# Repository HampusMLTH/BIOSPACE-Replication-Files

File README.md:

# BIOSPACE Replication Files

Here are files for replicating BIOSPACE as documented in Månefjord, H., M. Li, C. Brackmann, N. Reistad, A. Runemark, J. Rota, B. Anderson, J. T. Zoueu, A. Merdasa and M. Brydegaard (2022). "A biophotonic platform for quantitative analysis in the spatial, spectral, polarimetric, and goniometric domains." Review of Scientific Instruments 93(11).

Reach out to me if something is missing or unclear

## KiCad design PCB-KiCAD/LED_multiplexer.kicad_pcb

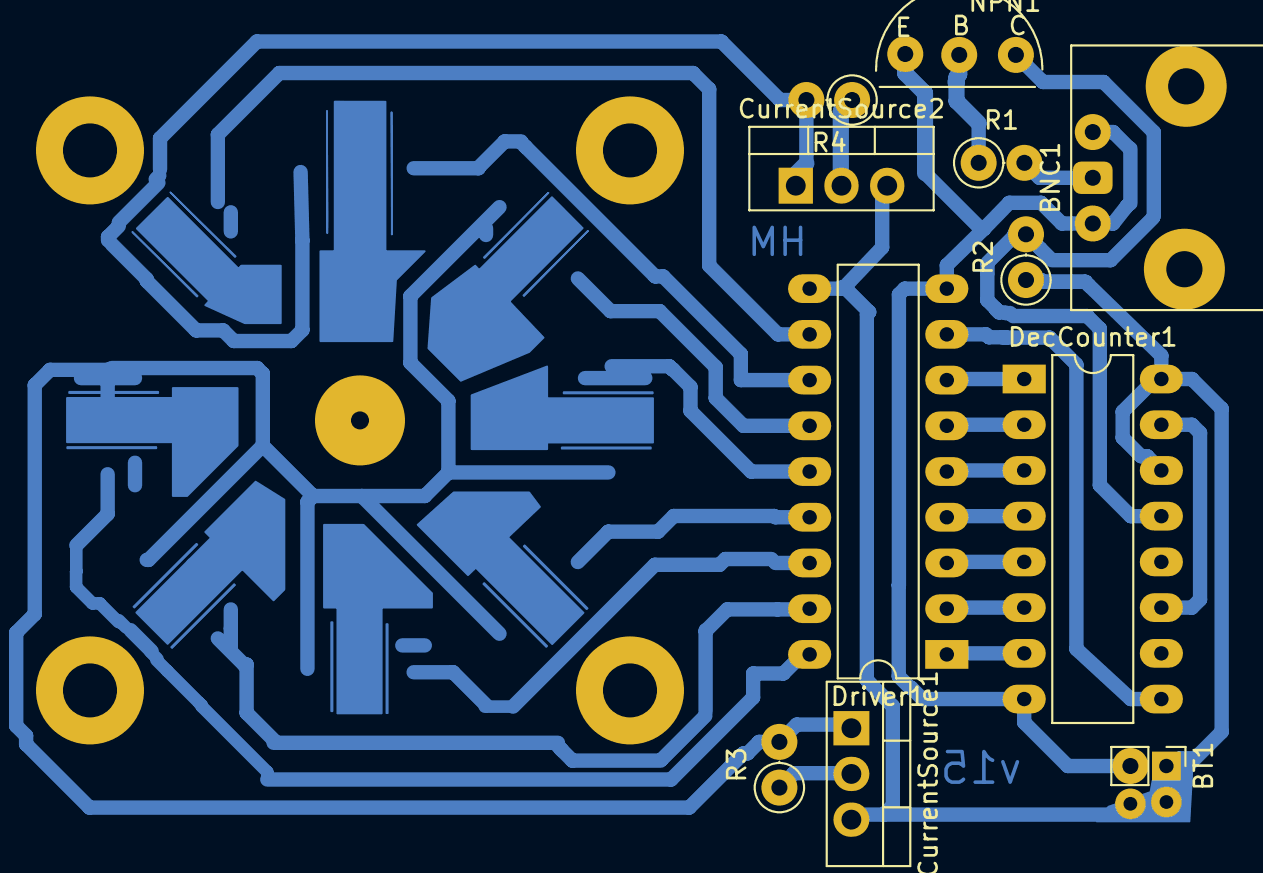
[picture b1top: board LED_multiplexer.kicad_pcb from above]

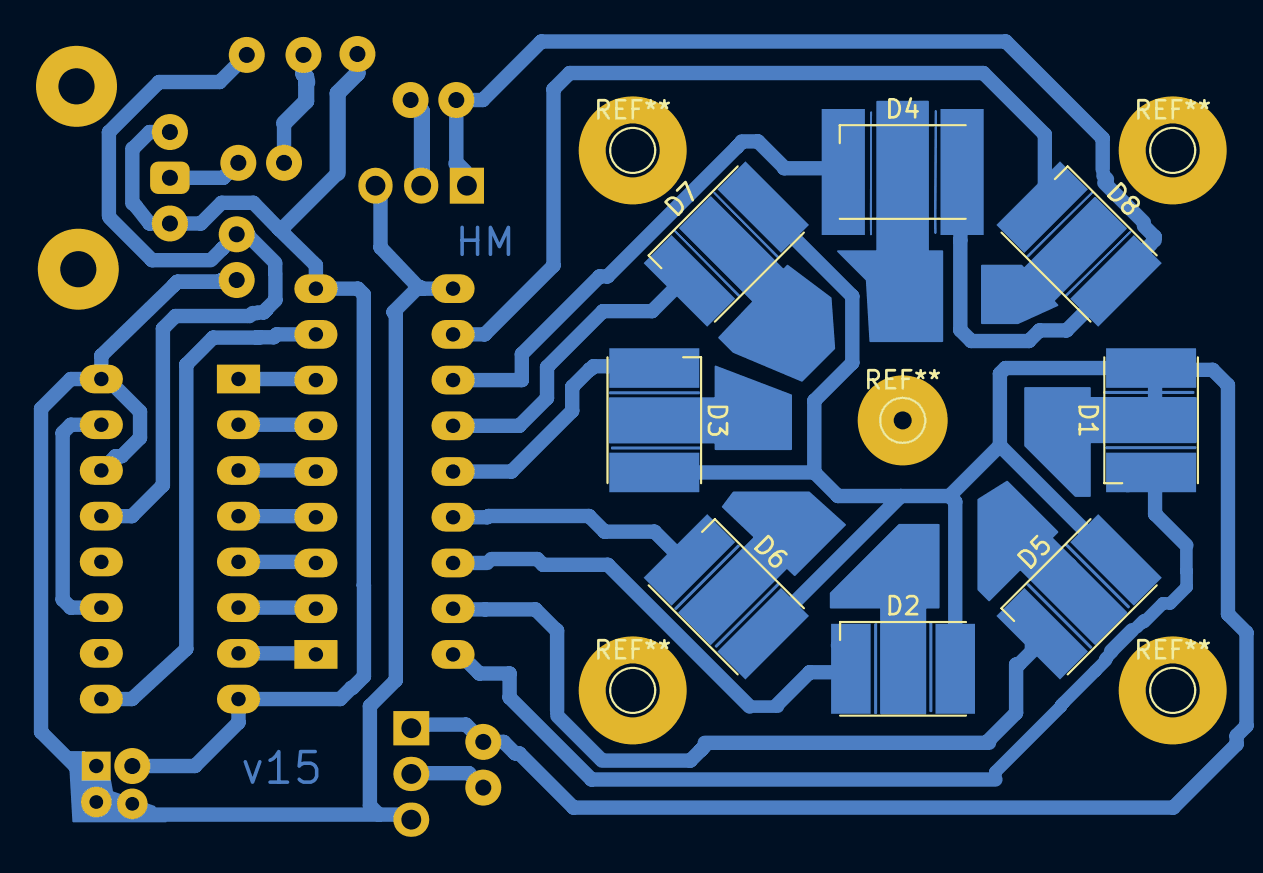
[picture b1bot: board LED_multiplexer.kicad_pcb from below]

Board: 2 copper layers, 19 parts (8 on the bottom side), 27 nets.

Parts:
BNC1: Coaxial; BNC_coax_Horizontal_c2
BT1: 9V; PinHeader_1x02_P2.00mm_Vertical_hampus
CurrentSource1, CurrentSource2: LM 317; TO-220-3_Vertical
D1: LEDs 365nm - 940nm; LED_SMB1N_5x5mm_sep_HS_right
D2, D3, D5, D6: LED; LED_SMB1N_5x5mm_sep_HS_right
D4: LED; LED_SMB1N_8x8mm_HS_left
D7, D8: LED; LED_SMB1N_5x5mm_sep_HS_left
DecCounter1: IC4017; DIP-16_W7.62mm_LongPads
Driver1: TBD62084A; DIP-18_W7.62mm_LongPads
NPN1: CMOS; pnp
R1, R2: 4k7; R_Axial_DIN0207_L6.3mm_D2.5mm_P2.54mm_Vertical
R3: 3.6; R_Axial_DIN0207_L6.3mm_D2.5mm_P2.54mm_Vertical
R4: 2.5; R_Axial_DIN0207_L6.3mm_D2.5mm_P2.54mm_Vertical

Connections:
GND: BNC1.2, BT1.2, DecCounter1.8, Driver1.9, NPN1.1
unnamed: BNC1.1, R1.1
unnamed: BT1.1, CurrentSource2.3
unnamed: CurrentSource1.1, D1.2, D2.2, D3.2, D5.2, D6.2, D7.2, R3.2
unnamed: CurrentSource1.2, R3.1
unnamed: CurrentSource2.1, D4.2, D8.2, R4.2
unnamed: CurrentSource2.2, R4.1
unnamed: D1.1, Driver1.18
unnamed: D2.1, Driver1.16
unnamed: D3.1, Driver1.14
unnamed: D4.1, Driver1.12
unnamed: D5.1, Driver1.17
unnamed: D6.1, Driver1.15
unnamed: D7.1, Driver1.13
unnamed: D8.1, Driver1.11
unnamed: DecCounter1.1, Driver1.7
unnamed: DecCounter1.2, Driver1.6
unnamed: DecCounter1.3, Driver1.5
unnamed: DecCounter1.4, Driver1.4
unnamed: DecCounter1.5, Driver1.3
unnamed: DecCounter1.6, Driver1.2
unnamed: DecCounter1.7, Driver1.1
unnamed: DecCounter1.9, Driver1.8
unnamed: DecCounter1.10, DecCounter1.15
unnamed: DecCounter1.13, NPN1.3, R2.2
unnamed: NPN1.2, R1.2
VCC: CurrentSource1.3, DecCounter1.14, DecCounter1.16, Driver1.10, R2.1

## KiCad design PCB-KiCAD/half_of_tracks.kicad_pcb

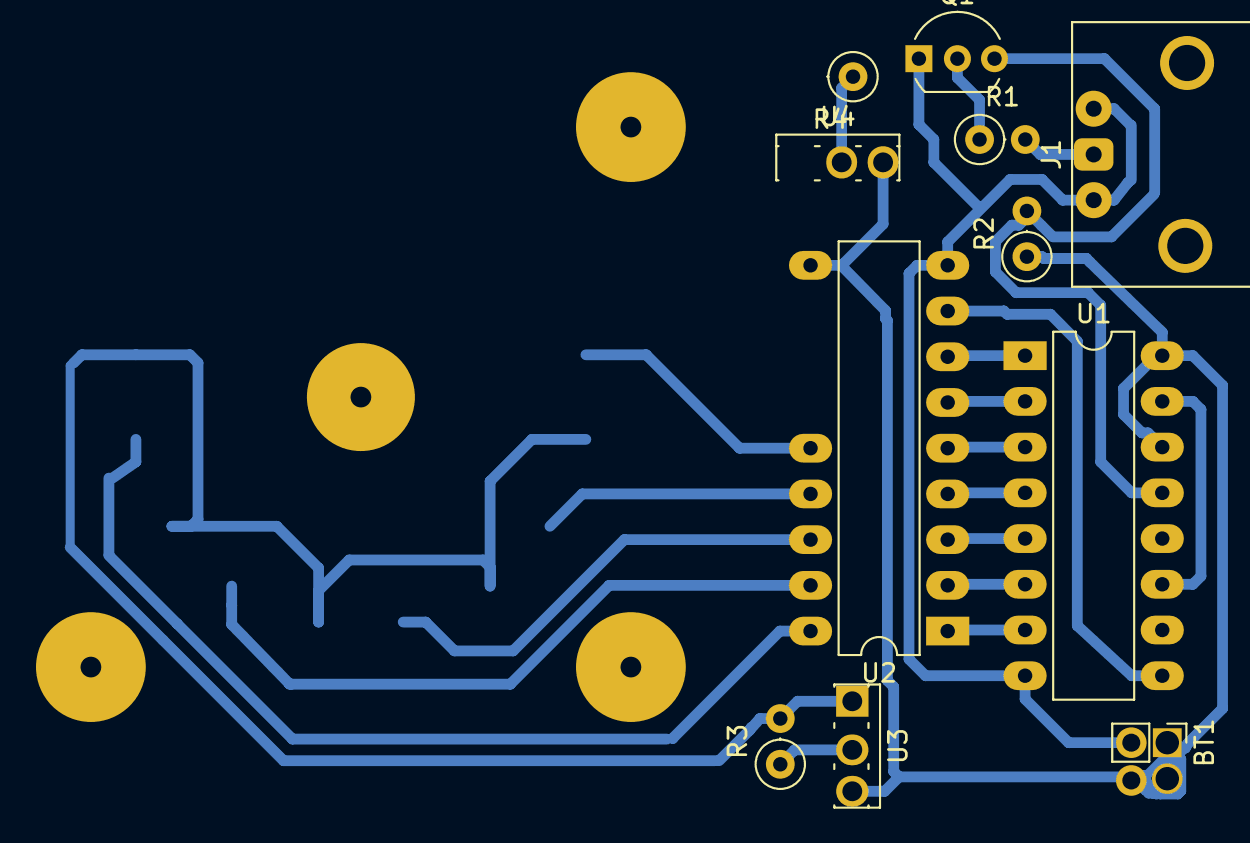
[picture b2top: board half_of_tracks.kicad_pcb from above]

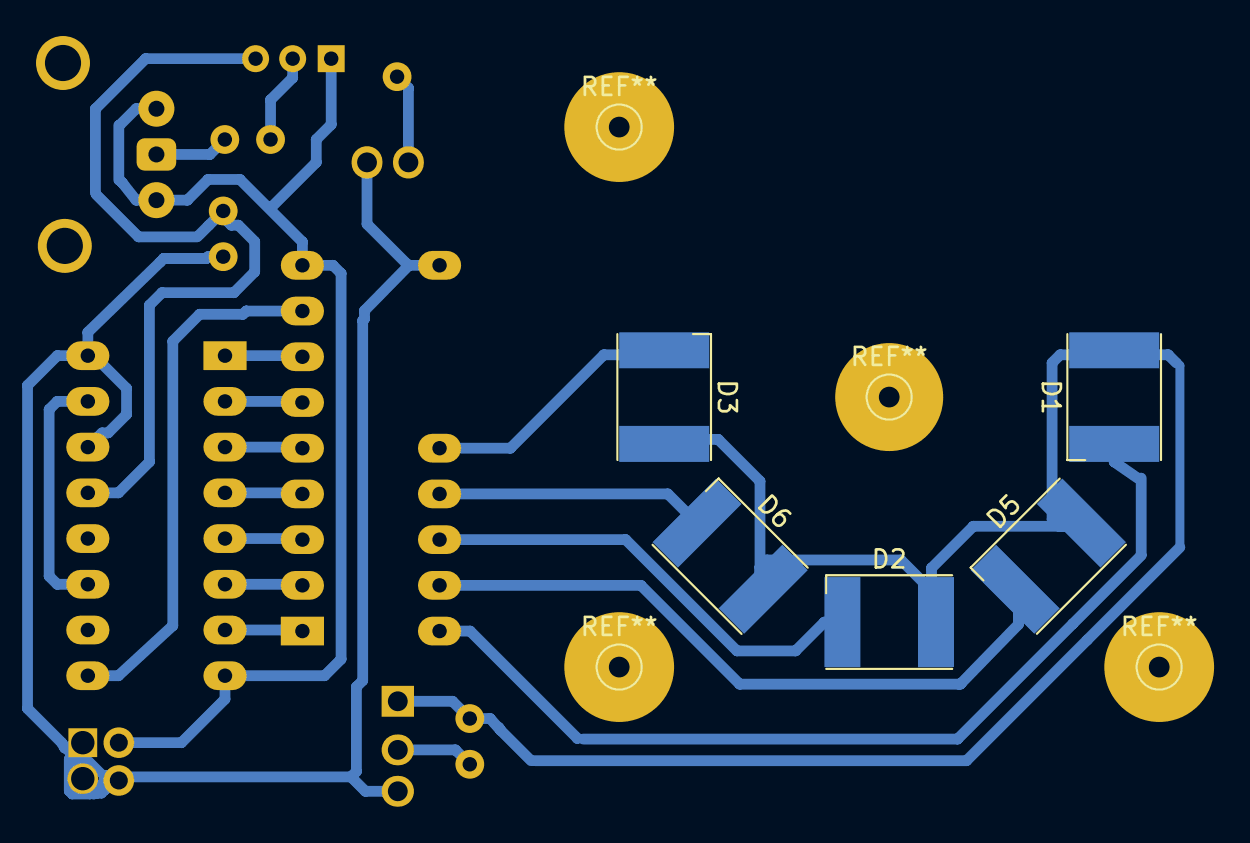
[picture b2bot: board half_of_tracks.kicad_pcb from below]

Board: 2 copper layers, 16 parts (5 on the bottom side), 22 nets.

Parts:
BT1: 9V; PinHeader_1x02_P2.00mm_Vertical_hampus
D1, D2, D3, D5, D6: LED; LED_SMB1N_5x5mm2
J1: Conn_Coaxial; BNC_coax_Horizontal_c2
Q1: 2N2219; NPN_tht_Inline_4mm2
R1, R2: 4k7; R_Axial_DIN0207_L6.3mm_D2.5mm_P2.54mm_Vertical
R3: 3.6; R_Axial_DIN0207_L6.3mm_D2.5mm_P2.54mm_Vertical
R4: 2.5; R_Axial_DIN0207_L6.3mm_D2.5mm_P2.54mm_Vertical_half
U1: IC4017; DIP-16_W7.62mm_LongPads
U2: TBD62084A; DIP-18_W7.62mm_LongPads_half
U3: LM317L_TO92; LM317
U4: LM317L_TO92; LM317_half

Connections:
GND: BT1.2, J1.2, Q1.1, U1.8, U2.9
unnamed: D1.1, U2.18
unnamed: D1.2, D2.2, D3.2, D5.2, D6.2, R3.2, U3.1
unnamed: D2.1, U2.16
unnamed: D3.1, U2.14
unnamed: D5.1, U2.17
unnamed: D6.1, U2.15
unnamed: J1.1, R1.2
unnamed: Q1.2, R1.1
unnamed: Q1.3, R2.2, U1.13
unnamed: R3.1, U3.2
unnamed: R4.1, U4.2
unnamed: U1.1, U2.7
unnamed: U1.2, U2.6
unnamed: U1.3, U2.5
unnamed: U1.4, U2.4
unnamed: U1.5, U2.3
unnamed: U1.6, U2.2
unnamed: U1.7, U2.1
unnamed: U1.9, U2.8
unnamed: U1.11, U1.15
VCC: BT1.1, R2.1, U1.14, U1.16, U2.10, U3.3, U4.3

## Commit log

2023-09-15 Added replication files
